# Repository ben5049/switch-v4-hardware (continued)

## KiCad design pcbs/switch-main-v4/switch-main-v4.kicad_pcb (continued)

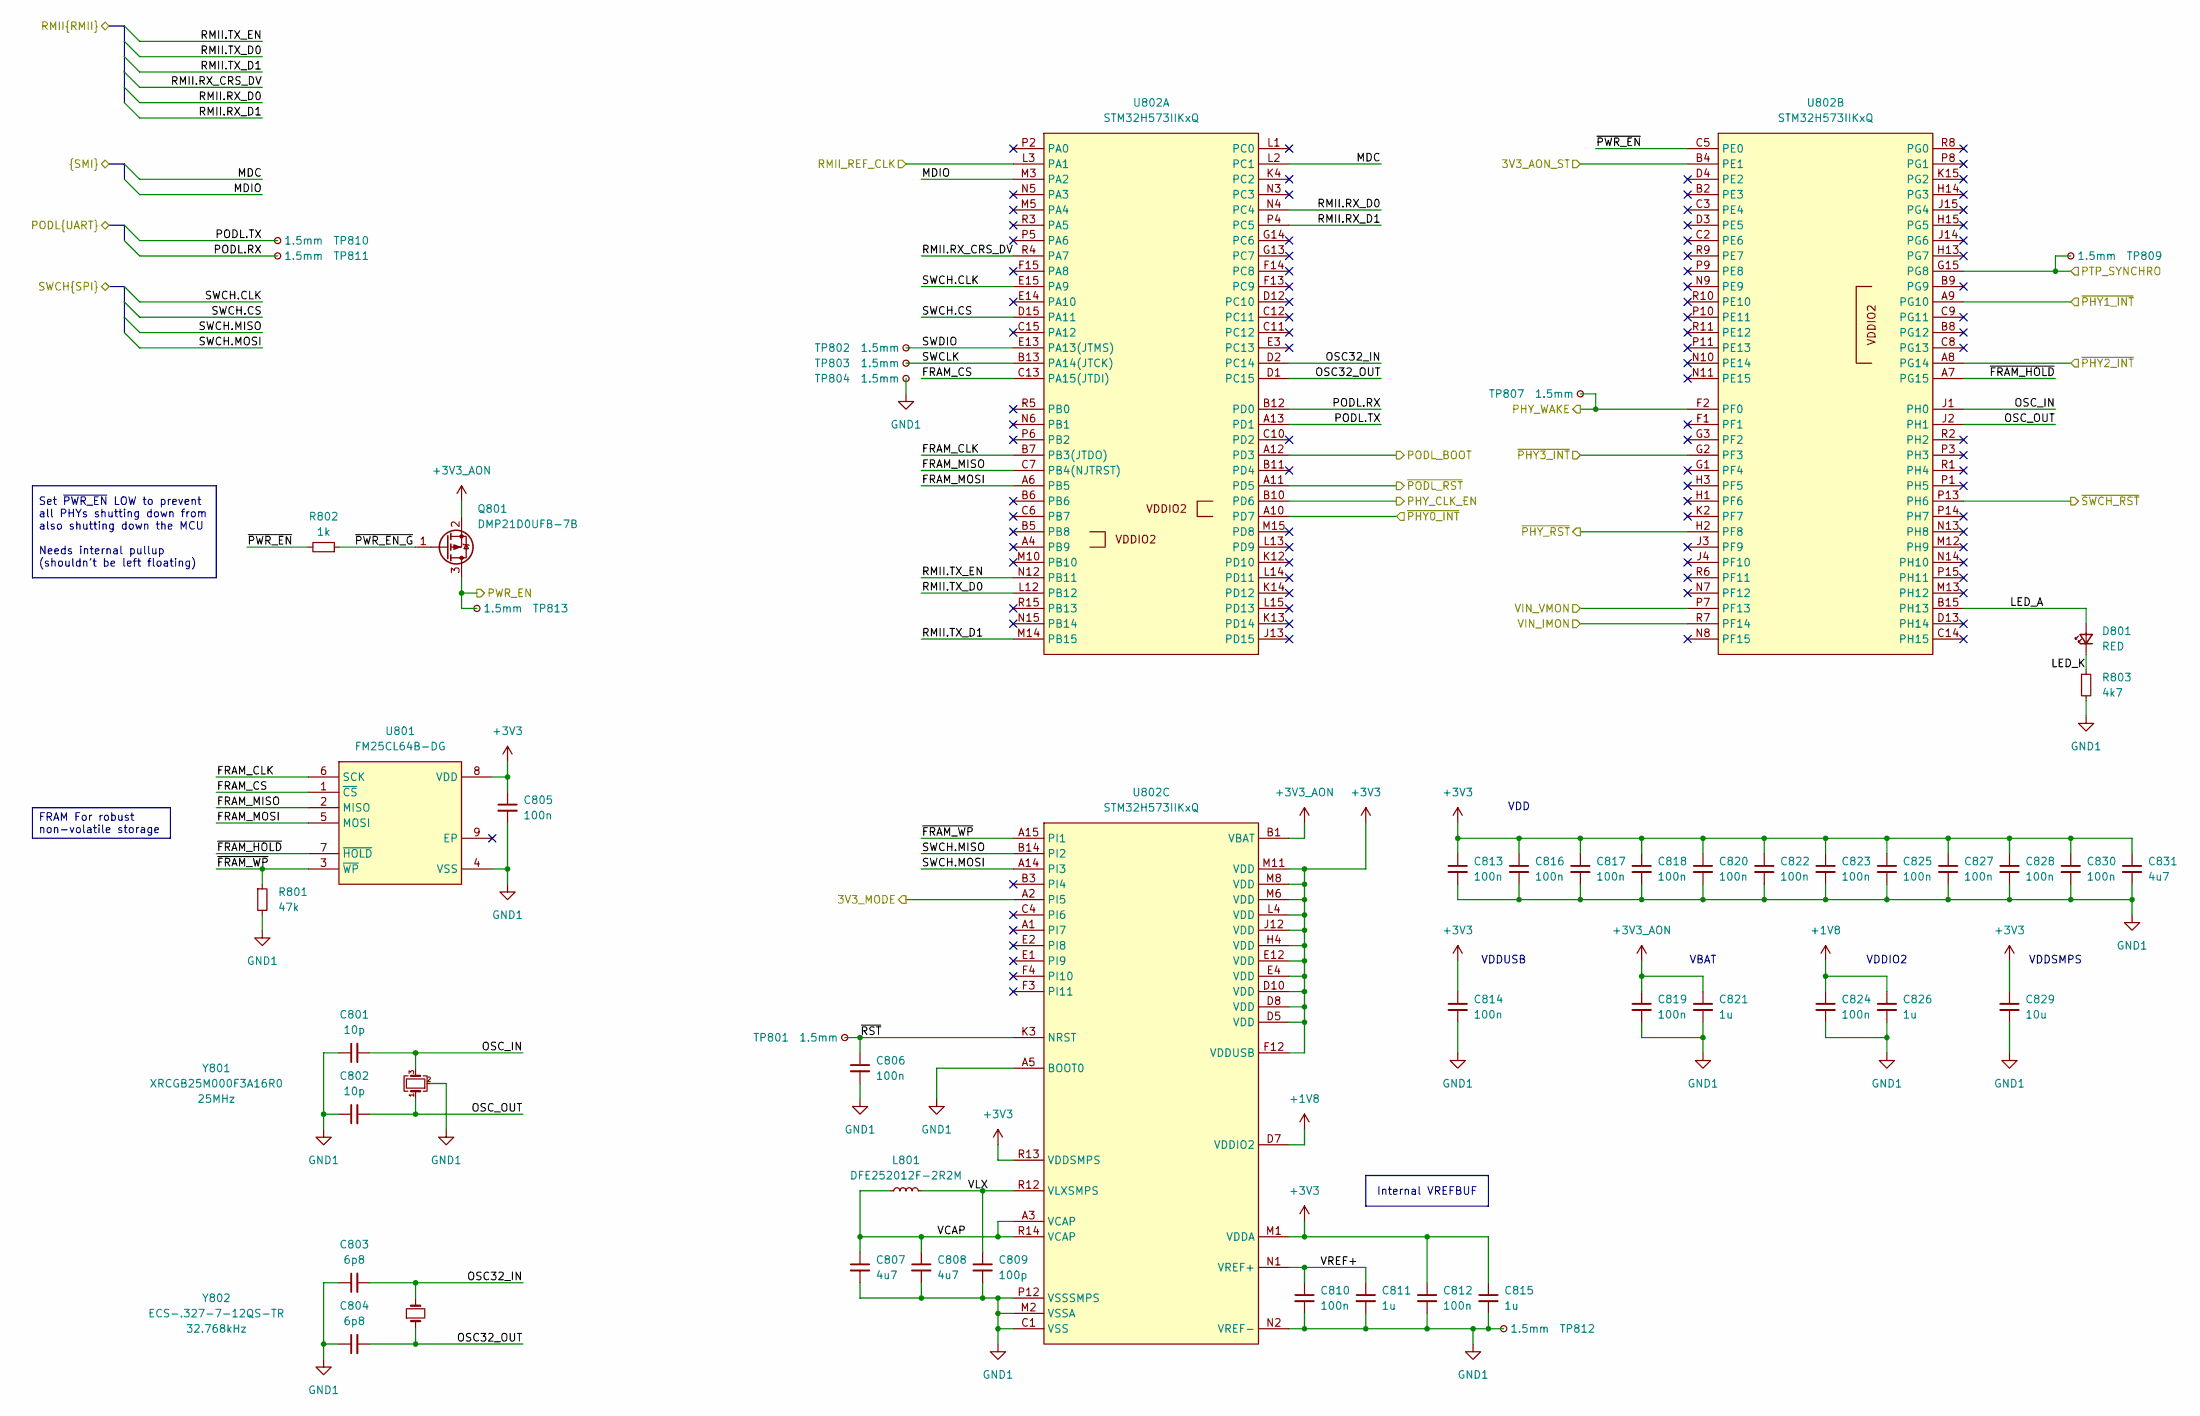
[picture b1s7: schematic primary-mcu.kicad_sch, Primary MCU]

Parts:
C801, C802: 10p; C_0402
C803, C804: 6p8; C_0402
C805, C806, C810, C812, C813, C814, C816, C817, C818, C819, C820, C822, C823, C824, C825, C827, C828, C830: 100n; C_0402
C807, C808, C831: 4u7; C_0402
C809: 100p; C_0402
C811, C815, C821, C826: 1u; C_0402
C829: 10u; C_0402
D801: RED; LED_0402_1005Metric
L801: DFE252012F-2R2M; L_1008_2520Metric
Q801: DMP21D0UFB-7B; DMP21D0UFB7B; Mouser Part Number 621-DMP21D0UFB-7B
R801: 47k; R_0402
R802: 1k; R_0402
R803: 4k7; R_0402
TP801, TP802, TP803, TP804, TP807, TP809, TP810, TP811, TP812, TP813: 1.5mm; TestPoint_Pad_D1.5mm
U801: FM25CL64B-DG; SON95P400X450X80-9N; Mouser Part Number 877-FM25CL64B-DG
U802: STM32H573IIKxQ; UFBGA-201_10x10mm_Layout15x15_P0.65mm
Y801: XRCGB25M000F3A16R0
Y802: ECS-.327-7-12QS-TR

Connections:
+1V8: C824.1, C826.1, U802.D7 (VDDIO2); also elsewhere on the board
+3V3: C805.1, C812.1, C813.1, C814.1, C815.1, C816.1, C817.1, C818.1, C820.1, C822.1, C823.1, C825.1, C827.1, C828.1, C829.1, C830.1, C831.1, U801.8 (VDD), U802.D5 (VDD), U802.D8 (VDD), U802.D10 (VDD), U802.E4 (VDD), U802.E12 (VDD), U802.F12 (VDDUSB), U802.H4 (VDD), U802.J12 (VDD), U802.L4 (VDD), U802.M1 (VDDA), U802.M6 (VDD), U802.M8 (VDD), U802.M11 (VDD), U802.R13 (VDDSMPS); also elsewhere on the board
+3V3_AON: C819.1, C821.1, Q801.2 (S), U802.B1 (VBAT); also elsewhere on the board
/Isolation Crossing/IN_C: U802.A12 (PD3); also elsewhere on the board
/Isolation Crossing/IN_D: U802.A11 (PD5); also elsewhere on the board
/PHYs/1000BASE-T1 PHY 0/INH: Q801.3 (D), TP813.1 (1_1); also elsewhere on the board
/PHYs/CLK_EN: U802.B10 (PD6); also elsewhere on the board
/PHYs/MDC: U802.L2 (PC1); also elsewhere on the board
/PHYs/MDIO: U802.M3 (PA2); also elsewhere on the board
/PHYs/WAKE: TP807.1 (1_1), U802.F2 (PF0); also elsewhere on the board
/PHYs/~PHY0_INT: U802.A10 (PD7); also elsewhere on the board
/PHYs/~PHY1_INT: U802.A9 (PG10); also elsewhere on the board
/PHYs/~PHY2_INT: U802.A8 (PG14); also elsewhere on the board
/PHYs/~PHY3_INT: U802.G2 (PF3); also elsewhere on the board
/PHYs/~RST: U802.H2 (PF8); also elsewhere on the board
/Power/3V3_AON_ST: U802.B4 (PE1); also elsewhere on the board
/Power/3V3_MODE: U802.A2 (PI5); also elsewhere on the board
/Power/VIN_IMON: U802.R7 (PF14); also elsewhere on the board
/Power/VIN_VMON: U802.P7 (PF13); also elsewhere on the board
/Primary MCU/FRAM_CLK: U801.6 (SCK), U802.B7 (PB3(JTDO))
/Primary MCU/FRAM_CS: U801.1 (~CS), U802.C13 (PA15(JTDI))
/Primary MCU/FRAM_MISO: U801.2 (MISO), U802.C7 (PB4(NJTRST))
/Primary MCU/FRAM_MOSI: U801.5 (MOSI), U802.A6 (PB5)
/Primary MCU/LED_A: D801.2 (A), U802.B15 (PH13)
/Primary MCU/LED_K: D801.1 (K), R803.1
/Primary MCU/OSC32_IN: C803.2, U802.D2 (PC14), Y802.2
/Primary MCU/OSC32_OUT: C804.2, U802.D1 (PC15), Y802.1
/Primary MCU/OSC_IN: C801.2, U802.J1 (PH0), Y801.3
/Primary MCU/OSC_OUT: C802.2, U802.J2 (PH1), Y801.1
/Primary MCU/PODL.RX: TP811.1 (1_1), U802.B12 (PD0); also elsewhere on the board
/Primary MCU/PODL.TX: TP810.1 (1_1), U802.A13 (PD1); also elsewhere on the board
/Primary MCU/PTP_SYNCHRO: TP809.1 (1_1), U802.G15 (PG8); also elsewhere on the board
/Primary MCU/RMII.RX_CRS_DV: U802.R4 (PA7); also elsewhere on the board
/Primary MCU/RMII.RX_D0: U802.N4 (PC4); also elsewhere on the board
/Primary MCU/RMII.RX_D1: U802.P4 (PC5); also elsewhere on the board
/Primary MCU/RMII.TX_D0: U802.L12 (PB12); also elsewhere on the board
/Primary MCU/RMII.TX_D1: U802.M14 (PB15); also elsewhere on the board
/Primary MCU/RMII.TX_EN: U802.N12 (PB11); also elsewhere on the board
/Primary MCU/RMII_REF_CLK: U802.L3 (PA1); also elsewhere on the board
/Primary MCU/SWCH.CLK: U802.E15 (PA9); also elsewhere on the board
/Primary MCU/SWCH.CS: U802.D15 (PA11); also elsewhere on the board
/Primary MCU/SWCH.MISO: U802.B14 (PI2); also elsewhere on the board
/Primary MCU/SWCH.MOSI: U802.A14 (PI3); also elsewhere on the board
/Primary MCU/SWCLK: TP803.1 (1_1), U802.B13 (PA14(JTCK))
/Primary MCU/SWDIO: TP802.1 (1_1), U802.E13 (PA13(JTMS))
/Primary MCU/VCAP: C807.1, C808.1, L801.2, U802.A3 (VCAP), U802.R14 (VCAP)
/Primary MCU/VLX: C809.1, L801.1, U802.R12 (VLXSMPS)
/Primary MCU/VREF+: C810.1, C811.1, U802.N1 (VREF+)
/Primary MCU/~FRAM_HOLD: U801.7 (~HOLD), U802.A7 (PG15)
/Primary MCU/~FRAM_WP: R801.1, U801.3 (~WP), U802.A15 (PI1)
/Primary MCU/~PWR_EN_G: Q801.1 (G), R802.1
/Primary MCU/~PWR_EN: R802.2, U802.C5 (PE0)
/Primary MCU/~RST: C806.1, TP801.1 (1_1), U802.K3 (NRST)
/Primary MCU/~SWCH_RST: U802.P13 (PH6); also elsewhere on the board
GND1: C801.1, C802.1, C803.1, C804.1, C805.2, C806.2, C807.2, C808.2, C809.2, C810.2, C811.2, C812.2, C813.2, C814.2, C815.2, C816.2, C817.2, C818.2, C819.2, C820.2, C821.2, C822.2, C823.2, C824.2, C825.2, C826.2, C827.2, C828.2, C829.2, C830.2, C831.2, R801.2, R803.2, TP804.1 (1_1), TP812.1 (1_1), U801.4 (VSS), U802.A5 (BOOT0), U802.C1 (VSS), U802.D6 (VSS), U802.D9 (VSS), U802.D11 (VSS), U802.D14 (VSS), U802.F6 (VSS), U802.F7 (VSS), U802.F8 (VSS), U802.F9 (VSS), U802.F10 (VSS), U802.G4 (VSS), U802.G6 (VSS), U802.G7 (VSS), U802.G8 (VSS), U802.G9 (VSS), U802.G10 (VSS), U802.G12 (VSS), U802.H6 (VSS), U802.H7 (VSS), U802.H8 (VSS), U802.H9 (VSS), U802.H10 (VSS), U802.H12 (VSS), U802.J6 (VSS), U802.J7 (VSS), U802.J8 (VSS), U802.J9 (VSS), U802.J10 (VSS), U802.K1 (VSS), U802.K6 (VSS), U802.K7 (VSS), U802.K8 (VSS), U802.K9 (VSS), U802.K10 (VSS), U802.M2 (VSSA), U802.M4 (VSS), U802.M7 (VSS), U802.M9 (VSS), U802.N2 (VREF-), U802.P12 (VSSSMPS), Y801.2 (G), Y801.4 (G); also elsewhere on the board

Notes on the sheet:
VBAT
VDDSMPS
VDDIO2
VDDUSB
VDD
FRAM For robust non-volatile storage
Internal VREFBUF
Set ~{PWR_EN} LOW to prevent all PHYs shutting down from also shutting down the MCU Needs internal pullup (shouldn't be left floating)

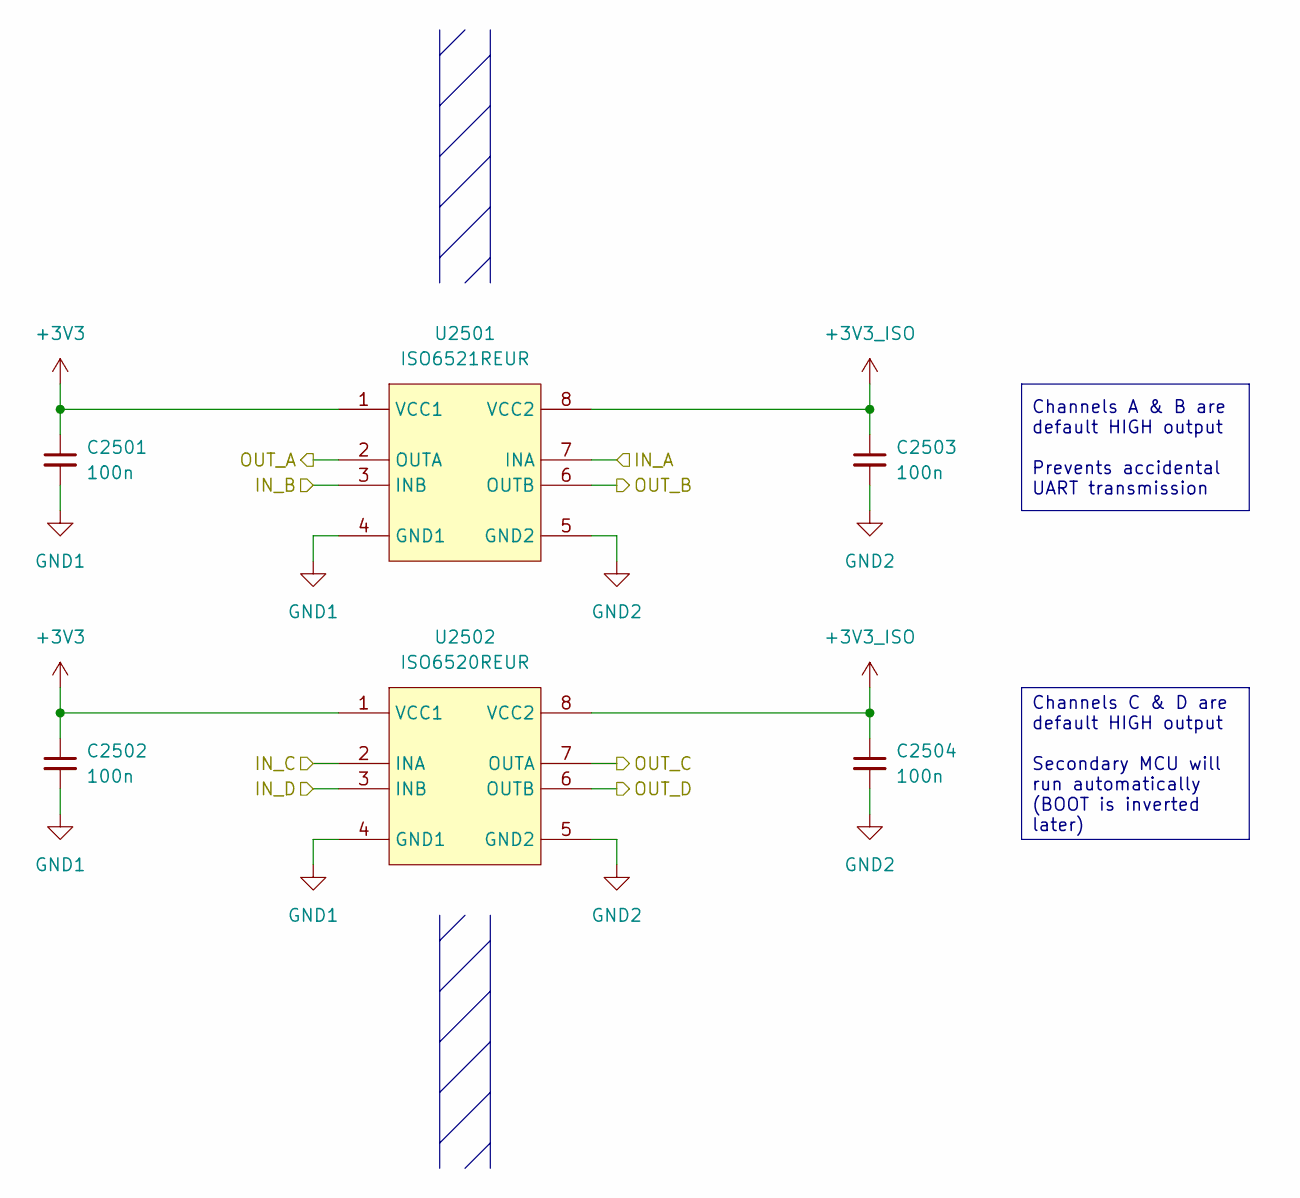
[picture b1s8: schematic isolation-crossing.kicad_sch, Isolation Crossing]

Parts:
C2501, C2502, C2503, C2504: 100n; C_0402
U2501: ISO6521REUR; SON50P300X200X105-8N-D; Mouser Part Number 595-ISO6521REUR
U2502: ISO6520REUR; SON50P300X200X105-8N-D

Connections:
+3V3: C2501.1, C2502.1, U2501.1 (VCC1), U2502.1 (VCC1); also elsewhere on the board
+3V3_ISO: C2503.1, C2504.1, U2501.8 (VCC2), U2502.8 (VCC2); also elsewhere on the board
/Isolation Crossing/IN_C: U2502.2 (INA); also elsewhere on the board
/Isolation Crossing/IN_D: U2502.3 (INB); also elsewhere on the board
/Isolation Crossing/OUT_C: U2502.7 (OUTA); also elsewhere on the board
/Isolation Crossing/OUT_D: U2502.6 (OUTB); also elsewhere on the board
/Primary MCU/PODL.RX: U2501.2 (OUTA); also elsewhere on the board
/Primary MCU/PODL.TX: U2501.3 (INB); also elsewhere on the board
/Secondary MCU/RX: U2501.6 (OUTB); also elsewhere on the board
/Secondary MCU/TX: U2501.7 (INA); also elsewhere on the board
GND1: C2501.2, C2502.2, U2501.4 (GND1), U2502.4 (GND1); also elsewhere on the board
GND2: C2503.2, C2504.2, U2501.5 (GND2), U2502.5 (GND2); also elsewhere on the board

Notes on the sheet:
Channels C & D are default HIGH output Secondary MCU will run automatically (BOOT is inverted later)
Channels A & B are default HIGH output Prevents accidental UART transmission

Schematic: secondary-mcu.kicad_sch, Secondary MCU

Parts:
C2601, C2602, C2603, C2604: 100n; C_0402
C2605, C2606, C2607: 4u7; C_0402
Q2601, Q2602: DMN21D2UFB-7B; DMN21D2UFB7B; Mouser Part Number 621-DMN21D2UFB-7B
R2601: 47k; R_0402
R2602, R2603: 4k7; R_0402
TP805, TP2601, TP2602, TP2603, TP2604: 1.5mm; TestPoint_Pad_D1.5mm
U2601: STM32H503KBUx; QFN-32-1EP_5x5mm_P0.5mm_EP3.45x3.45mm

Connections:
+2V5_ISO: C2603.1, C2605.1, U2601.5 (VDDA); also elsewhere on the board
+3V3_ISO: C2602.1, C2604.1, C2606.1, Q2602.1 (G), R2601.2, R2602.2, U2601.1 (VDD), U2601.17 (VDD); also elsewhere on the board
/CDNs & PoDL/PODL1.DET_EN: U2601.20 (PA9); also elsewhere on the board
/CDNs & PoDL/PODL1.DET_V+: U2601.10 (PA4); also elsewhere on the board
/CDNs & PoDL/PODL1.EN: U2601.19 (PA8); also elsewhere on the board
/CDNs & PoDL/PODL1.IMON: U2601.9 (PA3); also elsewhere on the board
/CDNs & PoDL/PODL2.DET_EN: U2601.2 (PC14); also elsewhere on the board
/CDNs & PoDL/PODL2.DET_V+: U2601.15 (PB1); also elsewhere on the board
/CDNs & PoDL/PODL2.EN: U2601.22 (PA12); also elsewhere on the board
/CDNs & PoDL/PODL2.IMON: U2601.12 (PA6); also elsewhere on the board
/CDNs & PoDL/PODL3.DET_EN: U2601.29 (PB6); also elsewhere on the board
/CDNs & PoDL/PODL3.DET_V+: U2601.14 (PB0); also elsewhere on the board
/CDNs & PoDL/PODL3.EN: U2601.30 (PB7); also elsewhere on the board
/CDNs & PoDL/PODL3.IMON: U2601.13 (PA7); also elsewhere on the board
/CDNs & PoDL/PODL_DIAG_EN: U2601.21 (PA11); also elsewhere on the board
/Isolation Crossing/OUT_C: Q2601.1 (G); also elsewhere on the board
/Isolation Crossing/OUT_D: Q2602.3 (D); also elsewhere on the board
/Power/2V5_ISO_EN: U2601.7 (PA1); also elsewhere on the board
/Power/3V3_ISO_MODE: U2601.28 (PB5); also elsewhere on the board
/Power/VIN_ISO_IMON: U2601.6 (PA0); also elsewhere on the board
/Power/VIN_ISO_VMON: U2601.8 (PA2); also elsewhere on the board
/Secondary MCU/NRST: C2601.1, R2603.1, TP2603.1 (1_1), U2601.4 (NRST)
/Secondary MCU/RX: U2601.25 (PA15(JTDI)); also elsewhere on the board
/Secondary MCU/SWCLK: TP2602.1 (1_1), U2601.24 (PA14(JTCK))
/Secondary MCU/SWDIO: TP2601.1 (1_1), U2601.23 (PA13(JTMS))
/Secondary MCU/TX: U2601.11 (PA5); also elsewhere on the board
/Secondary MCU/VCAP: C2607.1, U2601.16 (VCAP)
/Secondary MCU/~BOOT: Q2601.3 (D), R2601.1, TP2604.1 (1_1), U2601.31 (BOOT0)
/Secondary MCU/~RST_OD: Q2602.2 (S), R2602.1, R2603.2
GND2: C2601.2, C2602.2, C2603.2, C2604.2, C2605.2, C2606.2, C2607.2, Q2601.2 (S), TP805.1 (1_1), U2601.33 (VSS); also elsewhere on the board

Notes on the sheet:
Invert BOOT so it is LOW by default (flash boot)
Convert ~{RST} from a push-pull signal to an open drain signal (without inversion)

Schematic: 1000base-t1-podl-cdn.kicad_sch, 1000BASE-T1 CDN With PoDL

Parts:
C1901: 100n; C_0402
C1902: 100n; C_0603; Voltage 100V
C1903: 1n; C_0805; Voltage 1kV
D1901: 824012823; Mouser Part Number 710-824012823
D1902, D1903: SZESD7241N2T5G; SZESD7462N2T5G; Mouser Part Number 863-SZESD7241N2T5G
FL1901: ACT1210G-800-2P-TL10; ACT1210G; Mouser Part Number 810-ACT1210G8002PTL1
L1901, L1902: ADL3225VT-4R7M-TL000; ADL3225VT4R7MTL000; Mouser Part Number 810-ADL3225VT4R7MTL0
R1901: 100R; R_0402
T1901: 74930100

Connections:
/CDNs & PoDL/1000BASE-T1 PoDL CDN 1/CTP: C1901.1, T1901.5 (PM)
/CDNs & PoDL/1000BASE-T1 PoDL CDN 1/CTS1: C1902.2, T1901.4 (OUT1B)
/CDNs & PoDL/1000BASE-T1 PoDL CDN 1/CTS2: C1902.1, R1901.2, T1901.3 (OUT2A)
/CDNs & PoDL/1000BASE-T1 PoDL CDN 1/PWR+: L1902.3, L1902.4; also elsewhere on the board
/CDNs & PoDL/1000BASE-T1 PoDL CDN 1/TERM: C1903.1, R1901.1
/CDNs & PoDL/1000BASE-T1 PoDL CDN 1/TRXN: FL1901.2, T1901.2 (IN-)
/CDNs & PoDL/1000BASE-T1 PoDL CDN 1/TRXP: FL1901.1, T1901.1 (IN+)
/CDNs & PoDL/MDI1_IN.TRXN: D1901.1, D1901.6, FL1901.3; also elsewhere on the board
/CDNs & PoDL/MDI1_IN.TRXP: D1901.2, D1901.5, FL1901.4; also elsewhere on the board
/CDNs & PoDL/MDI1_OUT.TRXN: D1903.2 (A2), L1901.1, L1901.2, T1901.7 (OUT2B); also elsewhere on the board
/CDNs & PoDL/MDI1_OUT.TRXP: D1902.2 (A2), L1902.1, L1902.2, T1901.6 (OUT1A); also elsewhere on the board
GND1: C1901.2, D1901.3, D1901.4; also elsewhere on the board
GND2: L1901.3, L1901.4; also elsewhere on the board
SHIELD: C1903.2, D1902.1 (A1), D1903.1 (A1); also elsewhere on the board

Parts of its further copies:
C2001: 100n; C_0402
C2002: 100n; C_0603; Voltage 100V
C2003: 1n; C_0805; Voltage 1kV
D2001: 824012823; Mouser Part Number 710-824012823
D2002, D2003: SZESD7241N2T5G; SZESD7462N2T5G; Mouser Part Number 863-SZESD7241N2T5G
FL2001: ACT1210G-800-2P-TL10; ACT1210G; Mouser Part Number 810-ACT1210G8002PTL1
L2001, L2002: ADL3225VT-4R7M-TL000; ADL3225VT4R7MTL000; Mouser Part Number 810-ADL3225VT4R7MTL0
R2001: 100R; R_0402
T2001: 74930100

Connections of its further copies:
/CDNs & PoDL/1000BASE-T1 PoDL CDN 2/CTP: C2001.1, T2001.5 (PM)
/CDNs & PoDL/1000BASE-T1 PoDL CDN 2/CTS1: C2002.2, T2001.4 (OUT1B)
/CDNs & PoDL/1000BASE-T1 PoDL CDN 2/CTS2: C2002.1, R2001.2, T2001.3 (OUT2A)
/CDNs & PoDL/1000BASE-T1 PoDL CDN 2/PWR+: L2002.3, L2002.4; also elsewhere on the board
/CDNs & PoDL/1000BASE-T1 PoDL CDN 2/TERM: C2003.1, R2001.1
/CDNs & PoDL/1000BASE-T1 PoDL CDN 2/TRXN: FL2001.2, T2001.2 (IN-)
/CDNs & PoDL/1000BASE-T1 PoDL CDN 2/TRXP: FL2001.1, T2001.1 (IN+)
/CDNs & PoDL/MDI2_IN.TRXN: D2001.1, D2001.6, FL2001.3; also elsewhere on the board
/CDNs & PoDL/MDI2_IN.TRXP: D2001.2, D2001.5, FL2001.4; also elsewhere on the board
/CDNs & PoDL/MDI2_OUT.TRXN: D2003.2 (A2), L2001.1, L2001.2, T2001.7 (OUT2B); also elsewhere on the board
/CDNs & PoDL/MDI2_OUT.TRXP: D2002.2 (A2), L2002.1, L2002.2, T2001.6 (OUT1A); also elsewhere on the board
GND1: C2001.2, D2001.3, D2001.4; also elsewhere on the board
GND2: L2001.3, L2001.4; also elsewhere on the board
SHIELD: C2003.2, D2002.1 (A1), D2003.1 (A1); also elsewhere on the board

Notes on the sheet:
CMC
2x 100mΩ 720mA Max
Can also use LQH32NH3R3J23L
Termination
ESD Protection

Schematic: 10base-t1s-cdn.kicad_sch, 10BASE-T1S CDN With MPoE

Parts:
C2101: 100n; C_0402
C2102: 100n; C_0603; Voltage 100V
C2103: 1n; C_0805; Voltage 1kV
D2101: 824012823; Mouser Part Number 710-824012823
D2102, D2103: SZESD7241N2T5G; SZESD7462N2T5G; Mouser Part Number 863-SZESD7241N2T5G
FL2101: ACT1210E-131-2P-TL00; ACT1210E; Mouser Part Number 810-ACT1210E1312PTL0
L2101: MSD7342-333MLC_DM; MSD7342
L2102: MSD7342-333MLC; MSD7342
R2101: 3k3; R_0402
T2101: 74930100

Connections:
/CDNs & PoDL/10BASE-T1S CDN/CTP: C2101.1, T2101.5 (PM)
/CDNs & PoDL/10BASE-T1S CDN/CTS1: C2102.2, T2101.4 (OUT1B)
/CDNs & PoDL/10BASE-T1S CDN/CTS2: C2102.1, R2101.2, T2101.3 (OUT2A)
/CDNs & PoDL/10BASE-T1S CDN/MDI_PWR+: L2101.4 (2), L2102.3
/CDNs & PoDL/10BASE-T1S CDN/MDI_PWR-: L2101.1, L2102.4 (2)
/CDNs & PoDL/10BASE-T1S CDN/PWR+: L2102.1; also elsewhere on the board
/CDNs & PoDL/10BASE-T1S CDN/TERM: C2103.1, R2101.1
/CDNs & PoDL/10BASE-T1S CDN/TRXN: FL2101.2, T2101.2 (IN-)
/CDNs & PoDL/10BASE-T1S CDN/TRXP: FL2101.1, T2101.1 (IN+)
/CDNs & PoDL/MDI3_IN.TRXN: D2101.1, D2101.6, FL2101.3; also elsewhere on the board
/CDNs & PoDL/MDI3_IN.TRXP: D2101.2, D2101.5, FL2101.4; also elsewhere on the board
/CDNs & PoDL/MDI3_OUT.TRXN: D2103.2 (A2), L2101.3, T2101.7 (OUT2B); also elsewhere on the board
/CDNs & PoDL/MDI3_OUT.TRXP: D2102.2 (A2), L2101.2 (4), T2101.6 (OUT1A); also elsewhere on the board
GND1: C2101.2, D2101.3, D2101.4; also elsewhere on the board
GND2: L2102.2 (4); also elsewhere on the board
SHIELD: C2103.2, D2102.1 (A1), D2103.1 (A1); also elsewhere on the board

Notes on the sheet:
ESD Protection
Change termination resistor to 100Ω for end node
CMC
Termination
4x 270mΩ 760mA Max

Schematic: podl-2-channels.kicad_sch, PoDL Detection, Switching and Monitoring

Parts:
C2201, C2202: 100n; C_0402
D2201, D2202: PMEG4002EL-QYL
Q2201, Q2202, Q2204, Q2206: DMP21D0UFB-7B; DMP21D0UFB7B; Mouser Part Number 621-DMP21D0UFB-7B
Q2203, Q2205: DMN21D2UFB-7B; DMN21D2UFB7B; Mouser Part Number 621-DMN21D2UFB-7B
R2201, R2202, R2203, R2204, R2213, R2214, R2215, R2216: 4k7; R_0402
R2205: 470R; R_0402
R2206, R2210, R2217, R2221: 2k2; R_0402
R2207, R2209, R2212, R2218, R2220, R2223: 10k; R_0402
R2208, R2219: 1k; R_0402
R2211, R2222: 100k; R_0402
U2201, U2202: TPS27S100BRRK; TPS27S100ARRKR
Z2201, Z2202: BZX884-C3V3,315; BZX884; Mouser Part Number 771-BZX884-C3V9315

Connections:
+6V5_ISO: Q2201.2 (S), Q2202.2 (S), R2209.1, R2220.1; also elsewhere on the board
+VIN_ISO: U2201.9 (IN), U2201.10 (IN), U2201.11 (IN), U2201.12 (IN), U2202.9 (IN), U2202.10 (IN), U2202.11 (IN), U2202.12 (IN); also elsewhere on the board
/CDNs & PoDL/1000BASE-T1 PoDL CDN 1/PWR+: D2201.1 (K), R2211.1, U2201.5 (OUT), U2201.6 (OUT), U2201.7 (OUT), U2201.8 (OUT); also elsewhere on the board
/CDNs & PoDL/1000BASE-T1 PoDL CDN 2/PWR+: D2202.1 (K), R2222.1, U2202.5 (OUT), U2202.6 (OUT), U2202.7 (OUT), U2202.8 (OUT); also elsewhere on the board
/CDNs & PoDL/PODL1.DET_EN: R2207.1, R2208.1; also elsewhere on the board
/CDNs & PoDL/PODL1.DET_V+: R2211.2, R2212.1, Z2201.1 (K); also elsewhere on the board
/CDNs & PoDL/PODL1.EN: R2202.1; also elsewhere on the board
/CDNs & PoDL/PODL1.IMON: C2201.1, R2201.2, R2204.1; also elsewhere on the board
/CDNs & PoDL/PODL2.DET_EN: R2218.1, R2219.1; also elsewhere on the board
/CDNs & PoDL/PODL2.DET_V+: R2222.2, R2223.1, Z2202.1 (K); also elsewhere on the board
/CDNs & PoDL/PODL2.EN: R2214.1; also elsewhere on the board
/CDNs & PoDL/PODL2.IMON: C2202.1, R2213.2, R2216.1; also elsewhere on the board
/CDNs & PoDL/PODL_DIAG_EN: R2203.1, R2215.1; also elsewhere on the board
/CDNs & PoDL/PoDL (2 Channels)/CURRENT_MIRROR_GATE: Q2201.1 (G), Q2201.3 (D), Q2202.1 (G), R2205.1
/CDNs & PoDL/PoDL (2 Channels)/CURRENT_MIRROR_OUT: Q2202.3 (D), Q2204.2 (S), Q2206.2 (S)
/CDNs & PoDL/PoDL (2 Channels)/DIAG_EN1: R2203.2, U2201.14 (DIAG_EN)
/CDNs & PoDL/PoDL (2 Channels)/DIAG_EN2: R2215.2, U2202.14 (DIAG_EN)
/CDNs & PoDL/PoDL (2 Channels)/EN1: R2202.2, U2201.3 (EN)
/CDNs & PoDL/PoDL (2 Channels)/EN2: R2214.2, U2202.3 (EN)
/CDNs & PoDL/PoDL (2 Channels)/G1: Q2203.1 (G), R2208.2
/CDNs & PoDL/PoDL (2 Channels)/G2: Q2203.3 (D), Q2204.1 (G), R2209.2
/CDNs & PoDL/PoDL (2 Channels)/G3: Q2205.1 (G), R2219.2
/CDNs & PoDL/PoDL (2 Channels)/G4: Q2205.3 (D), Q2206.1 (G), R2220.2
/CDNs & PoDL/PoDL (2 Channels)/ILIM1: R2210.2, U2201.15 (ILIM)
/CDNs & PoDL/PoDL (2 Channels)/ILIM2: R2221.2, U2202.15 (ILIM)
/CDNs & PoDL/PoDL (2 Channels)/IMON1: R2204.2, R2206.2, U2201.16 (IMON)
/CDNs & PoDL/PoDL (2 Channels)/IMON2: R2216.2, R2217.2, U2202.16 (IMON)
/CDNs & PoDL/PoDL (2 Channels)/I_PODL1: D2201.2 (A), Q2204.3 (D)
/CDNs & PoDL/PoDL (2 Channels)/I_PODL2: D2202.2 (A), Q2206.3 (D)
GND2: C2201.2, C2202.2, Q2203.2 (S), Q2205.2 (S), R2201.1, R2205.2, R2206.1, R2207.2, R2210.1, R2212.2, R2213.1, R2217.1, R2218.2, R2221.1, R2223.2, U2201.2 (GND), U2201.17 (EP), U2202.2 (GND), U2202.17 (EP), Z2201.2 (A), Z2202.2 (A); also elsewhere on the board

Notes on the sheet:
Power Switch 2
Current Source (Mirror)
Current Switches
Power Switch 1
1.1A Maximum output current 1.1A Maximum measurable current
If the output is shorted the current is still limited to 14mA, and 91mW will be dissapated (in spec)
Each channel can be enabled individually to check for PoDL devices. Since the outputs share a current source, only one channel can be checked at a time.
I_{OUT} = 0.28046 * V_{MON}
6.5 / 470 = ~14mA Within the 9-16mA PoDL spec
1/11 Potential divider and zener clamp to protect the 3V3 microcontroller IO.
During the detection phase, 9-16mA is sent into TRXP and the resulting voltage is measured. If a PoDL compatible device is detected on the other end (indicated by a 4.05-4.55V zener diode) then the full 24V is enabled.
IMON can go up to 4.75V, potential divider limits this to be withing 2.5V ADC range.

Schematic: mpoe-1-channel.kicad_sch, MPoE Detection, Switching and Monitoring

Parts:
C2301, C2302: 100n; C_0402
D2301: PMEG4002EL-QYL
F2301: 0603L008YR; Fuse_0603_1608Metric
Q2301: DMN21D2UFB-7B; DMN21D2UFB7B; Mouser Part Number 621-DMN21D2UFB-7B
Q2302: DMP21D0UFB-7B; DMP21D0UFB7B; Mouser Part Number 621-DMP21D0UFB-7B
R2301: 10k; R_0402
R2302: 1k; R_0402
R2303: 100k; R_0402
R2304, R2306, R2307, R2308: 4k7; R_0402
R2305: 1R; R_0402
R2309, R2310: 2k2; R_0402
U2301: NCS213RMUTAG; Mouser Part Number 863-NCS213RMUTAG
U2302: TPS27S100BRRK; TPS27S100ARRKR

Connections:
+2V5_ISO: C2302.2, U2301.6 (VS); also elsewhere on the board
+6V5_ISO: Q2302.2 (S), R2303.2; also elsewhere on the board
+VIN_ISO: U2302.9 (IN), U2302.10 (IN), U2302.11 (IN), U2302.12 (IN); also elsewhere on the board
/CDNs & PoDL/10BASE-T1S CDN/PWR+: D2301.1 (K), U2302.5 (OUT), U2302.6 (OUT), U2302.7 (OUT), U2302.8 (OUT); also elsewhere on the board
/CDNs & PoDL/MPoE (1 Channel)/DET: Q2301.1 (G), R2302.1
/CDNs & PoDL/MPoE (1 Channel)/DET+: Q2302.3 (D), R2305.1, U2301.2 (IN+), U2301.3 (IN+)
/CDNs & PoDL/MPoE (1 Channel)/DET-: F2301.2, R2305.2, U2301.4 (IN-), U2301.5 (IN-)
/CDNs & PoDL/MPoE (1 Channel)/DET_FUSED: D2301.2 (A), F2301.1
/CDNs & PoDL/MPoE (1 Channel)/DIAG_EN: R2307.2, U2302.14 (DIAG_EN)
/CDNs & PoDL/MPoE (1 Channel)/EN: R2306.2, U2302.3 (EN)
/CDNs & PoDL/MPoE (1 Channel)/ILIM: R2310.2, U2302.15 (ILIM)
/CDNs & PoDL/MPoE (1 Channel)/IMON: R2308.2, R2309.2, U2302.16 (IMON)
/CDNs & PoDL/MPoE (1 Channel)/~DET: Q2301.3 (D), Q2302.1 (G), R2303.1
/CDNs & PoDL/PODL3.DET_EN: R2301.2, R2302.2; also elsewhere on the board
/CDNs & PoDL/PODL3.DET_V+: U2301.10 (OUT); also elsewhere on the board
/CDNs & PoDL/PODL3.EN: R2306.1; also elsewhere on the board
/CDNs & PoDL/PODL3.IMON: C2301.1, R2304.2, R2308.1; also elsewhere on the board
/CDNs & PoDL/PODL_DIAG_EN: R2307.1; also elsewhere on the board
GND2: C2301.2, C2302.1, Q2301.2 (S), R2301.1, R2304.1, R2309.1, R2310.1, U2301.8 (REF), U2301.9 (GND), U2302.2 (GND), U2302.17 (EP); also elsewhere on the board

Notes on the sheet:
IMON can go up to 4.75V, potential divider limits this to be withing 2.5V ADC range.
Fuse protects against short circuit output
During detection, the bus is powered at 6.5V, and each PD draws 1mA for every watt they require. This is detected as a voltage drop across the 1 ohm resistor.
1.1A Maximum output current 1.1A Maximum measurable current
I_{OUT} = 0.28046 * V_{MON}

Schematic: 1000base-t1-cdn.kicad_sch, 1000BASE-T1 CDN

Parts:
C1801: 100n; C_0402
C1802: 100n; C_0603; Voltage 100V
C1803: 1n; C_0805; Voltage 1kV
D1801: 824012823; Mouser Part Number 710-824012823
D1802, D1803: SZESD7241N2T5G; SZESD7462N2T5G; Mouser Part Number 863-SZESD7241N2T5G
FL1801: ACT1210G-800-2P-TL10; ACT1210G; Mouser Part Number 810-ACT1210G8002PTL1
R1801: 100R; R_0402
T1801: 74930100

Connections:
/CDNs & PoDL/1000BASE-T1 CDN/CTP: C1801.1, T1801.5 (PM)
/CDNs & PoDL/1000BASE-T1 CDN/CTS1: C1802.2, T1801.4 (OUT1B)
/CDNs & PoDL/1000BASE-T1 CDN/CTS2: C1802.1, R1801.2, T1801.3 (OUT2A)
/CDNs & PoDL/1000BASE-T1 CDN/TERM: C1803.1, R1801.1
/CDNs & PoDL/1000BASE-T1 CDN/TRXN: FL1801.2, T1801.2 (IN-)
/CDNs & PoDL/1000BASE-T1 CDN/TRXP: FL1801.1, T1801.1 (IN+)
/CDNs & PoDL/MDI0_IN.TRXN: D1801.1, D1801.6, FL1801.3; also elsewhere on the board
/CDNs & PoDL/MDI0_IN.TRXP: D1801.2, D1801.5, FL1801.4; also elsewhere on the board
/CDNs & PoDL/MDI0_OUT.TRXN: D1803.2 (A2), T1801.7 (OUT2B); also elsewhere on the board
/CDNs & PoDL/MDI0_OUT.TRXP: D1802.2 (A2), T1801.6 (OUT1A); also elsewhere on the board
GND1: C1801.2, D1801.3, D1801.4; also elsewhere on the board
SHIELD0: C1803.2, D1802.1 (A1), D1803.1 (A1); also elsewhere on the board

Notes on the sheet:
Termination
ESD Protection
CMC

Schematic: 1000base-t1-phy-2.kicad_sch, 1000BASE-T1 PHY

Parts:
C1501, C1502, C1505, C1506, C1507: 4u7; C_0402
C1503: 22p; C_0402
C1504, C1508, C1509, C1510, C1511, C1513, C1514, C1515, C1516, C1517, C1518, C1519, C1520: 100n; C_0402
C1512, C1521: 10u; C_0402
C1522: 10u; C_0402; not fitted
L1501: 78438313015; L_Wurth_WE-MAIA-1610; Part Number 78438313015
Q1501: DMN21D2UFB-7B; DMN21D2UFB7B; Mouser Part Number 621-DMN21D2UFB-7B
Q1502: DMP21D0UFB-7B; DMP21D0UFB7B; Mouser Part Number 621-DMP21D0UFB-7B
R1501, R1503: 4k7; R_0402
R1502: 10k; R_0402; not fitted
R1504: 4k7; R_0402; not fitted
R1505: 180k; R_0402
R1506: 360k; R_0402
R1507: 4k99; R_0402
R1508: 1k; R_0402
R1509: 47k; R_0402
TP1501, TP1502: 1.5mm; TestPoint_Pad_D1.5mm
U1501: TPS62290TDRVRQ1; SON65P200X200X80-7N; Mouser Part Number 595-TPS62290TDRVRQ1
U1502: 88Q2112-A2-NYD2A000-P123; 88Q2112

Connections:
+1V8: C1509.1, C1511.1, C1512.1, C1513.1, C1515.1, C1517.1, C1519.1, C1521.1, R1502.2, U1502.9 (AVDD18), U1502.24 (VDDO), U1502.33 (AVDD18), U1502.40 (VDDO); also elsewhere on the board
+3V3: C1501.1, C1502.1, C1508.1, C1510.1, U1501.2 (MODE), U1501.5 (VIN), U1502.6 (AVDD33); also elsewhere on the board
+3V3_AON: C1514.1, Q1502.2 (S), R1509.2, U1502.46 (VLPR); also elsewhere on the board
/CDNs & PoDL/MDI2_IN.TRXN: U1502.5 (MDIN); also elsewhere on the board
/CDNs & PoDL/MDI2_IN.TRXP: U1502.4 (MDIP); also elsewhere on the board
/PHYs/1000BASE-T1 PHY 0/INH: Q1502.3 (D), U1501.4 (EN); also elsewhere on the board
/PHYs/1000BASE-T1 PHY 0/MDC: U1502.38 (MDC); also elsewhere on the board
/PHYs/1000BASE-T1 PHY 0/MDIO: U1502.39 (MDIO); also elsewhere on the board
/PHYs/1000BASE-T1 PHY 0/~RST: U1502.36 (~RST); also elsewhere on the board
/PHYs/1000BASE-T1 PHY 2/0V9: C1503.1, C1505.1, C1506.1, C1507.1, C1516.1, C1518.1, C1520.1, C1522.1, L1501.2, R1505.1, TP1501.1 (1_1), U1502.17 (DVDD), U1502.43 (DVDD)
/PHYs/1000BASE-T1 PHY 2/CLKIN: C1504.2; also elsewhere on the board
/PHYs/1000BASE-T1 PHY 2/FB: C1503.2, R1505.2, R1506.1, U1501.3 (FB)
/PHYs/1000BASE-T1 PHY 2/GPIO: R1504.2, U1502.42 (GPIO/PHYAD2)
/PHYs/1000BASE-T1 PHY 2/INH_G: Q1501.1 (G), R1508.1
/PHYs/1000BASE-T1 PHY 2/INH_OUT: R1508.2, U1502.45 (INH)
/PHYs/1000BASE-T1 PHY 2/RSET: R1507.2, U1502.1 (RSET)
/PHYs/1000BASE-T1 PHY 2/SW: L1501.1, U1501.1 (SW)
/PHYs/1000BASE-T1 PHY 2/XTAL_IN: C1504.1, U1502.12 (XTAL_IN)
/PHYs/1000BASE-T1 PHY 2/~INH: Q1501.3 (D), Q1502.1 (G), R1509.1
/PHYs/WAKE: U1502.44 (WAKE_IN); also elsewhere on the board
/PHYs/xMII2.RX_CLK: U1502.23 (RCLK); also elsewhere on the board
/PHYs/xMII2.RX_CTL: R1503.2, U1502.22 (RXC); also elsewhere on the board
/PHYs/xMII2.RX_D0: U1502.21 (RXD0/PHYAD0); also elsewhere on the board
/PHYs/xMII2.RX_D1: R1501.2, U1502.20 (RXD1/PHYAD1); also elsewhere on the board
/PHYs/xMII2.RX_D2: U1502.19 (RXD2/MODE0); also elsewhere on the board
/PHYs/xMII2.RX_D3: U1502.18 (RXD3/MODE1); also elsewhere on the board
/PHYs/xMII2.TX_CLK: U1502.25 (TCLK); also elsewhere on the board
/PHYs/xMII2.TX_CTL: U1502.26 (TXC); also elsewhere on the board
/PHYs/xMII2.TX_D0: U1502.27 (TXD0); also elsewhere on the board
/PHYs/xMII2.TX_D1: U1502.28 (TXD1); also elsewhere on the board
/PHYs/xMII2.TX_D2: U1502.29 (TXD2); also elsewhere on the board
/PHYs/xMII2.TX_D3: U1502.30 (TXD3); also elsewhere on the board
/PHYs/~PHY2_INT: R1502.1, U1502.37 (~INT); also elsewhere on the board
GND1: C1501.2, C1502.2, C1505.2, C1506.2, C1507.2, C1508.2, C1509.2, C1510.2, C1511.2, C1512.2, C1513.2, C1514.2, C1515.2, C1516.2, C1517.2, C1518.2, C1519.2, C1520.2, C1521.2, C1522.2, Q1501.2 (S), R1501.1, R1503.1, R1504.1, R1506.2, R1507.1, TP1502.1 (1_1), U1501.6 (GND), U1501.7 (EP), U1502.11 (VSSC), U1502.49 (VSS); also elsewhere on the board

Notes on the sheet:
AVDD18: 145mA Typ 152mA Max
RSET Must be 1% tolerance
Use high quality, low ESR (<50mΩ) capacitors such as GRM155R61A475ME02
Populating strapping pulldowns means that bit of the PHY address or mode will be 1.
AVDD33: 25mA Typ 27mA Max
VDDO: 18.6mA Typ
DVDD: 202mA Typ 359mA Max
This INH circuit is non-standard, and requires testing.
MODE[1:0] = 0x00 means the PHY will start as a 100BASE-T1 master, 0x01 means 100BASE-T1 slave.
Maximum allowed noise on any supply is 50mV peak to peak
Internal GPIO pullups needed for ~{INT}.

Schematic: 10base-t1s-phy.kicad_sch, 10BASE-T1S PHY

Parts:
C1601, C1602, C1603: 10u; C_0402
C1604, C1605, C1606, C1610: 100n; C_0402
C1607, C1608, C1609, C1611: 10n; C_0402
R1601, R1602, R1604, R1605, R1606, R1607: 10k; R_0402
R1603: 10k; R_0402; not fitted
R1608: 12k4; R_0402
U1601: LAN8671C2-E_U3B; QFN50P400X400X100-25N-D; Mouser Part Number 579-LAN8671C2-E/U3B

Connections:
+3V3: C1601.1, C1602.1, C1604.1, C1605.1, C1607.1, C1608.1, C1610.1, C1611.1, R1601.1, R1603.1, R1605.1, U1601.6 (VDDP_1), U1601.13 (VDDP_2), U1601.22 (VDDA); also elsewhere on the board
+3V3_AON: C1603.1, C1606.1, C1609.1, U1601.18 (VDDAU); also elsewhere on the board
/CDNs & PoDL/MDI3_IN.TRXN: U1601.24 (TRXN); also elsewhere on the board
/CDNs & PoDL/MDI3_IN.TRXP: U1601.23 (TRXP); also elsewhere on the board
/PHYs/10BASE-T1S PHY/PTP_TS: U1601.7 (GPIO0)
/PHYs/10BASE-T1S PHY/RBIAS: R1608.1, U1601.19 (RBIAS)
/PHYs/10BASE-T1S PHY/WAKE_OUT: U1601.17 (WAKE_OUT)
/PHYs/1000BASE-T1 PHY 0/INH: U1601.2 (INH); also elsewhere on the board
/PHYs/MDC: U1601.9 (MDC); also elsewhere on the board
/PHYs/MDIO: U1601.10 (MDIO); also elsewhere on the board
/PHYs/WAKE: U1601.1 (WAKE_IN); also elsewhere on the board
/PHYs/xMII3.RX_CRS_DV: R1607.1, U1601.14 (CRSDV/PHYAD1); also elsewhere on the board
/PHYs/xMII3.RX_D0: R1604.1, U1601.11 (RXD0/PHYAD2); also elsewhere on the board
/PHYs/xMII3.RX_D1: R1605.2, U1601.12 (RXD1/PHYAD3); also elsewhere on the board
/PHYs/xMII3.RX_ER: R1606.1, U1601.15 (RXER/PHYAD0); also elsewhere on the board
/PHYs/xMII3.TX_D0: U1601.4 (TXD0); also elsewhere on the board
/PHYs/xMII3.TX_D1: U1601.3 (TXD1); also elsewhere on the board
/PHYs/xMII3.TX_EN: R1602.1, U1601.5 (TXEN); also elsewhere on the board
/PHYs/xMII3_REF_CLK: U1601.20 (REFCLKIN); also elsewhere on the board
/PHYs/~PHY3_INT: R1601.2, U1601.16 (IRQ_N); also elsewhere on the board
/PHYs/~RST: R1603.2, U1601.8 (RESET_N); also elsewhere on the board
GND1: C1601.2, C1602.2, C1603.2, C1604.2, C1605.2, C1606.2, C1607.2, C1608.2, C1609.2, C1610.2, C1611.2, R1602.2, R1604.2, R1606.2, R1607.2, R1608.2, U1601.25 (VSS); also elsewhere on the board

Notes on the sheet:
VDDA: 34mA Typ 41mA Max
PHY_ADDR = 0x0008
VDDP: 4mA Typ
The first time VDDAU is powered up it asserts INH (HIGH).
VDDAU: 0.57mA Typ
RBIAS must be +-1%

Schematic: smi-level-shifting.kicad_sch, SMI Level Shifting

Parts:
Q1101, Q1102, Q1103: DMN21D2UFB-7B; DMN21D2UFB7B; Mouser Part Number 621-DMN21D2UFB-7B
R1101, R1102, R1104, R1105: 1k5; R_0402
R1103, R1106: 10k; R_0402
TP1101, TP1102: 1.5mm; TestPoint_Pad_D1.5mm

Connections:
+1V8: Q1101.1 (G), Q1102.1 (G), Q1103.1 (G), R1104.2, R1105.2, R1106.2; also elsewhere on the board
+3V3: R1101.2, R1102.2, R1103.2; also elsewhere on the board
/PHYs/1000BASE-T1 PHY 0/MDC: Q1101.2 (S), R1104.1, TP1102.1 (1_1); also elsewhere on the board
/PHYs/1000BASE-T1 PHY 0/MDIO: Q1102.2 (S), R1105.1, TP1101.1 (1_1); also elsewhere on the board
/PHYs/1000BASE-T1 PHY 0/~RST: Q1103.2 (S), R1106.1; also elsewhere on the board
/PHYs/MDC: Q1101.3 (D), R1101.1; also elsewhere on the board
/PHYs/MDIO: Q1102.3 (D), R1102.1; also elsewhere on the board
/PHYs/~RST: Q1103.3 (D), R1103.1; also elsewhere on the board

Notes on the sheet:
The 1000BASE-T1 PHYs operate at a 1V8 logic level (to save RGMII power), but the SMI and ~{RST} pins operate at a 3V3 logic level. Level shifting is used to allow communication.
